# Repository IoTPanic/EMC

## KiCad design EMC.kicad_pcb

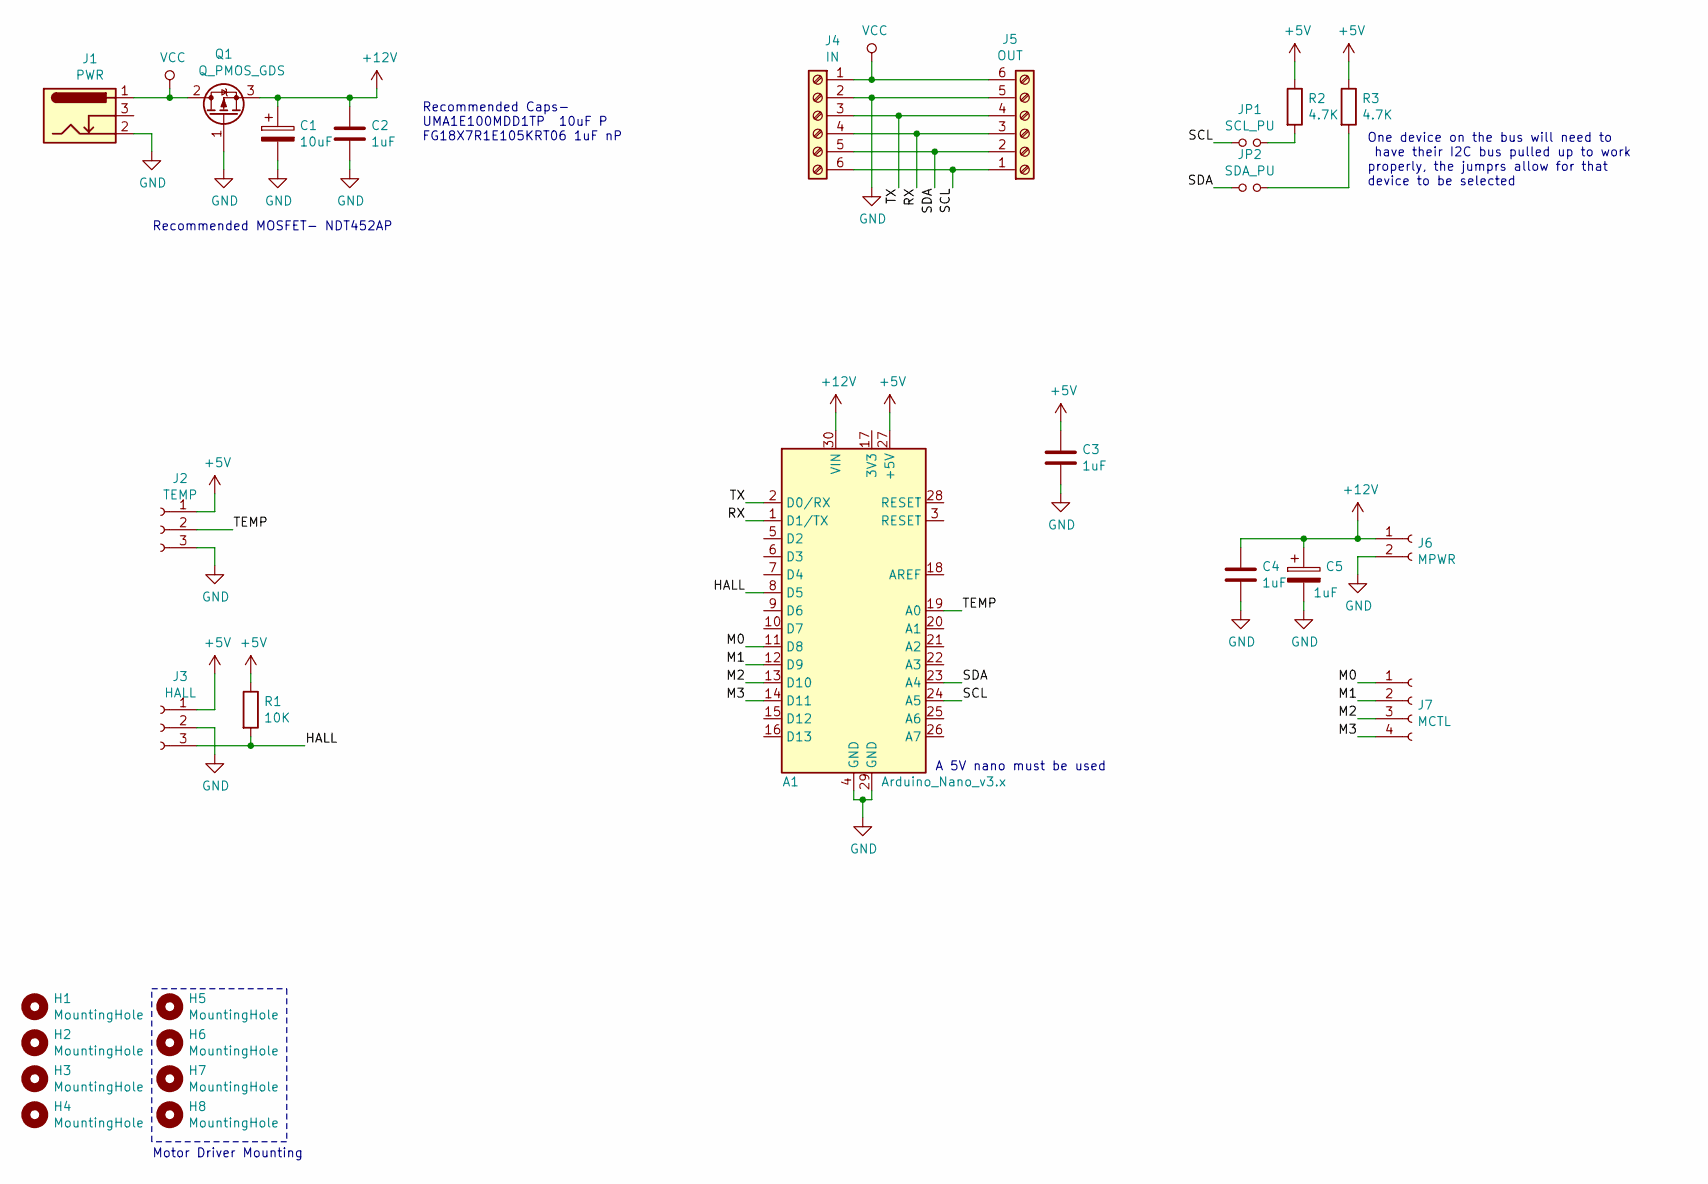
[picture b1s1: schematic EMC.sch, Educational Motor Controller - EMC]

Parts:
A1: Arduino_Nano_v3.x; Arduino_Nano_WithMountingHoles
C1: 10uF; CP_Radial_D5.0mm_P2.50mm
C2, C3, C4: 1uF; C_Disc_D3.4mm_W2.1mm_P2.50mm
C5: 1uF; CP_Radial_D5.0mm_P2.50mm
H1, H2, H3, H4, H5, H6, H7, H8: MountingHole; MountingHole_3.2mm_M3
J1: PWR; BarrelJack_Horizontal
J2: TEMP; PinHeader_1x03_P2.54mm_Vertical
J3: HALL; PinHeader_1x03_P2.54mm_Vertical
J4: IN; TerminalBlock_bornier-6_P5.08mm
J5: OUT; TerminalBlock_bornier-6_P5.08mm
J6: MPWR; PinHeader_1x02_P2.54mm_Vertical
J7: MCTL; PinHeader_1x04_P2.54mm_Vertical
JP1: SCL_PU; SolderJumper-2_P1.3mm_Open_TrianglePad1.0x1.5mm
JP2: SDA_PU; SolderJumper-2_P1.3mm_Open_TrianglePad1.0x1.5mm
Q1: Q_PMOS_GDS; SOT-223-3_TabPin2
R1: 10K; R_Axial_DIN0204_L3.6mm_D1.6mm_P5.08mm_Horizontal
R2, R3: 4.7K; R_Axial_DIN0204_L3.6mm_D1.6mm_P5.08mm_Horizontal

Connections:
+5V: A1.27 (+5V), C3.1, J2.1, J3.1, R1.1, R2.1, R3.1
+12V: A1.30 (VIN), C1.1, C2.1, C4.1, C5.1, J6.1, Q1.3 (S)
/HALL: A1.8 (D5), J3.3, R1.2
/M0: A1.11 (D8), J7.1
/M1: A1.12 (D9), J7.2
/M2: A1.13 (D10), J7.3
/M3: A1.14 (D11), J7.4
/RX: A1.1 (D1/TX), J4.4, J5.3
/SCL: A1.24 (A5), J4.6, J5.1, JP1.1
/SDA: A1.23 (A4), J4.5, J5.2, JP2.1
/TEMP: A1.19 (A0), J2.2
/TX: A1.2 (D0/RX), J4.3, J5.4
GND: A1.4 (GND), A1.29 (GND), C1.2, C2.2, C3.2, C4.2, C5.2, J1.2, J2.3, J3.2, J4.2, J5.5, J6.2, Q1.1 (G)
unnamed: JP1.2, R2.2
unnamed: JP2.2, R3.2
VCC: J1.1, J4.1, J5.6, Q1.2 (D)

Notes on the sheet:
Motor Driver Mounting
One device on the bus will need to have their I2C bus pulled up to work properly, the jumprs allow for that device to be selected
A 5V nano must be used
Recommended Caps- UMA1E100MDD1TP 10uF P FG18X7R1E105KRT06 1uF nP
Recommended MOSFET- NDT452AP

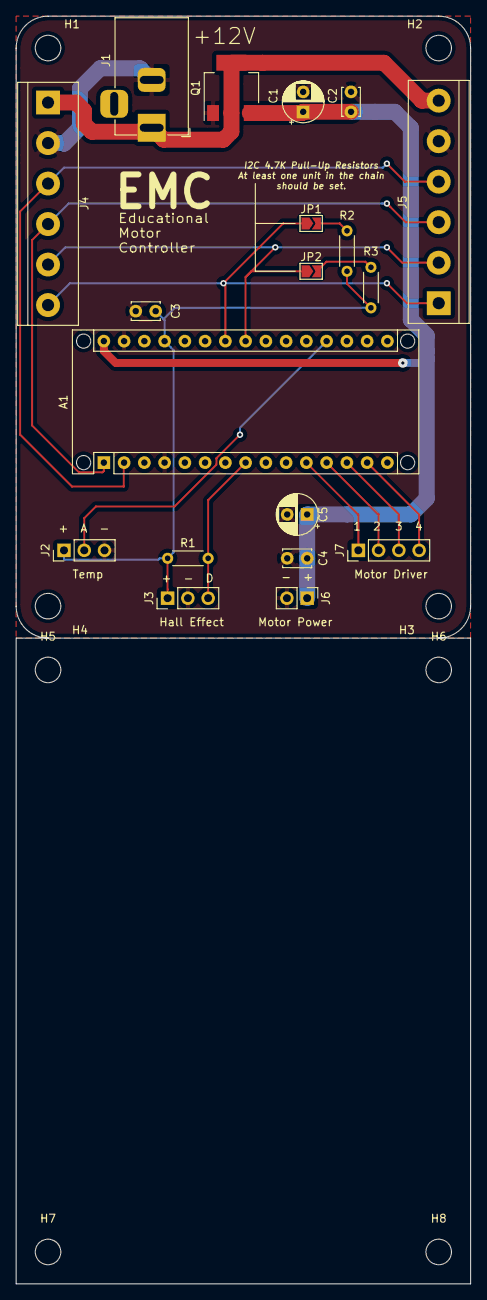
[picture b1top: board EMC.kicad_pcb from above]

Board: 2 copper layers, 56.9 x 158.9 mm, 27 parts (0 on the bottom side), 16 nets.

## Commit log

2019-11-05 Small fixes
